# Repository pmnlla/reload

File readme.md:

temp repo before this is moved to hackclub/reflow

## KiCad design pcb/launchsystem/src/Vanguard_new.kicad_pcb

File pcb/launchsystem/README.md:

Rocket launch system - data logging, multiple safety switches, etc

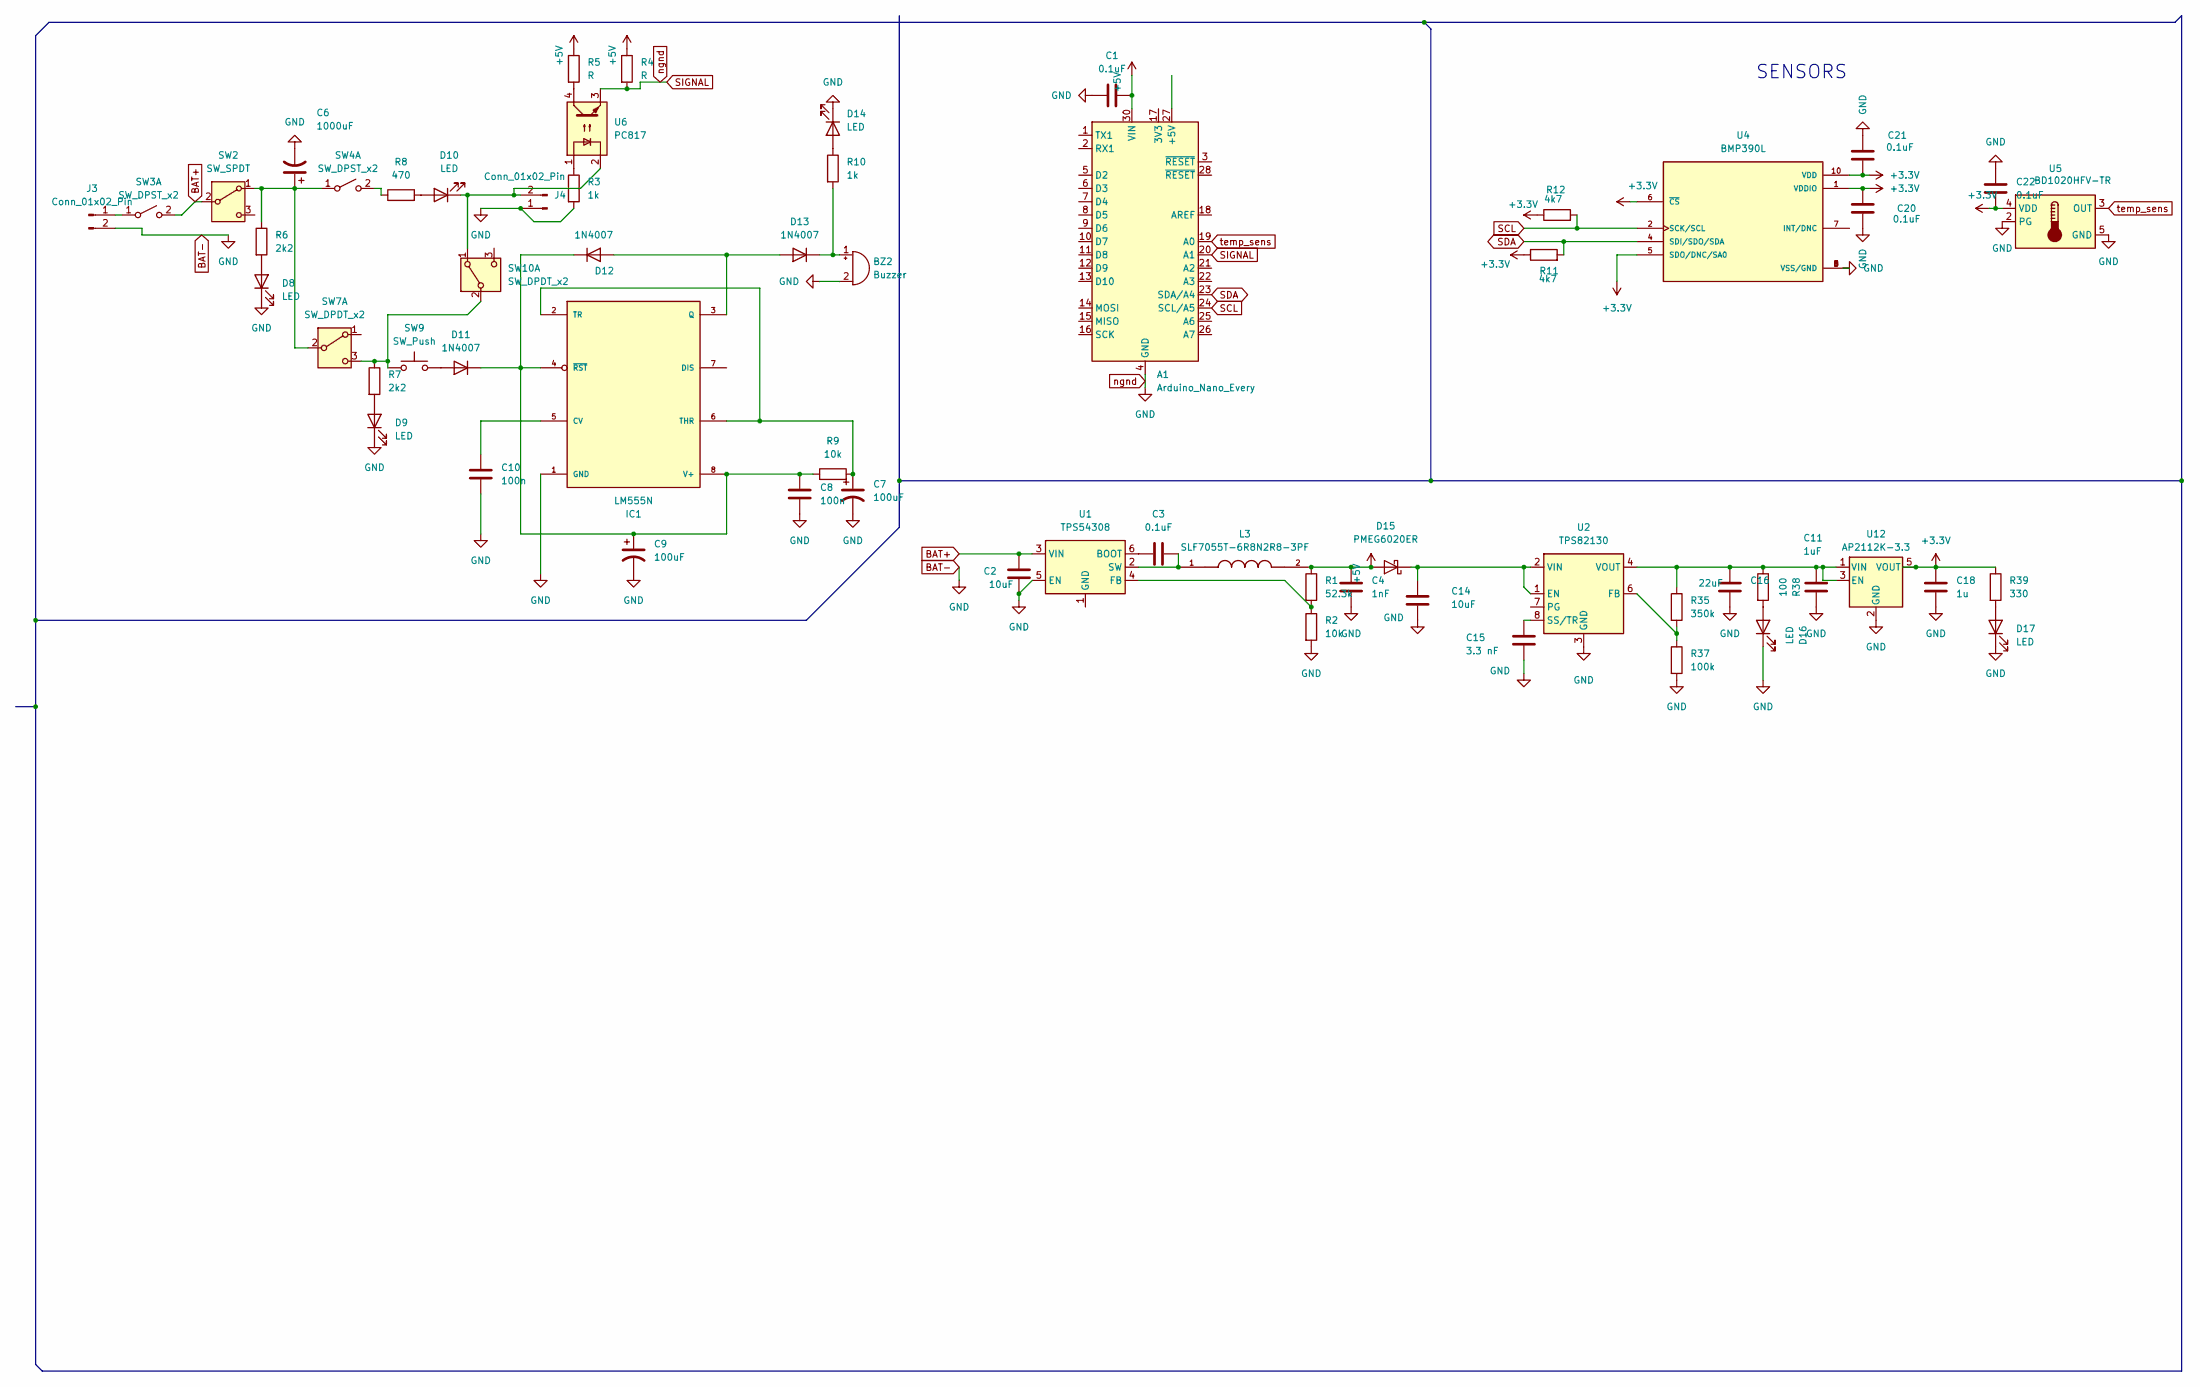
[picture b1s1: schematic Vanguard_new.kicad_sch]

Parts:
A1: Arduino_Nano_Every; Arduino_Nano
BZ2: Buzzer; Buzzer_12x9.5RM7.6
C1, C3, C20, C21, C22: 0.1uF; C_0805_2012Metric
C2, C14: 10uF; C_0805_2012Metric
C4: 1nF; C_0805_2012Metric
C6: 1000uF; C_0805_2012Metric
C7, C9: 100uF; C_0805_2012Metric
C8, C10: 100n; C_0805_2012Metric
C11: 1uF; C_0805_2012Metric
C15: 3.3 nF; C_0805_2012Metric
C16: 22uF; C_0805_2012Metric
C18: 1u; C_0805_2012Metric
D8, D9, D10, D14: LED; LED_D3.0mm
D11, D12, D13: 1N4007; D_SOD-123F
D15: PMEG6020ER; Nexperia_CFP3_SOD-123W
D16, D17: LED; LED_0201_0603Metric
IC1: LM555N; SOIC-8_3.9x4.9mm_P1.27mm
J3: Conn_01x02_Pin; AMASS_XT60-F_1x02_P7.20mm_Vertical
J4: Conn_01x02_Pin; PinSocket_1x02_P2.54mm_Vertical
L3: SLF7055T-6R8N2R8-3PF; L_7.3x7.3_H4.5; PARTREV N/A
R1: 52.3k; R_0805_2012Metric
R2, R9: 10k; R_0805_2012Metric
R3, R10: 1k; R_0805_2012Metric
R4, R5: R; R_0805_2012Metric
R6, R7: 2k2; R_0805_2012Metric
R8: 470; R_0805_2012Metric
R11, R12: 4k7; R_0805_2012Metric
R35: 350k; R_0805_2012Metric
R37: 100k; R_0805_2012Metric
R38: 100; R_0805_2012Metric
R39: 330; R_0805_2012Metric
SW2: SW_SPDT; PinHeader_1x03_P2.54mm_Vertical
SW3, SW4: SW_DPST_x2; PinHeader_1x02_P2.54mm_Vertical
SW7, SW10: SW_DPDT_x2; PinHeader_1x03_P2.54mm_Vertical
SW9: SW_Push; PinHeader_1x02_P2.54mm_Vertical
U1: TPS54308; SOT-23-6
U2: TPS82130; Texas_SIL0008D_MicroSiP-8-1EP_2.8x3mm_P0.65mm_EP1.1x1.9mm_T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
U4: BMP390L; ST_HLGA-10_2x2mm_P0.5mm_LayoutBorder3x2y; PARTREV 1.7
U5: BD1020HFV-TR; HVSOF5
U6: PC817; DIP-4_W7.62mm
U12: AP2112K-3.3; SOT-23-5

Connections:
+3.3V: C18.1, C20.2, C21.1, C22.2, R11.1, R12.1, R39.1, U4.1 (VDDIO), U4.5 (SDO/DNC/SA0), U4.6 (~CS), U4.10 (VDD), U5.4 (VDD), U12.5 (VOUT)
+5V: A1.30 (VIN), C1.2, C4.1, D15.2 (A), L3.2, R1.1, R4.1, R5.1
BAT+: C2.1, SW2.2 (B), SW3.2 (B), U1.3 (VIN)
BAT-: A1.4 (GND), A1.20 (A1), A1.29 (GND), BZ2.2 (-), C1.1, C2.2, C4.2, C6.2, C7.2, C8.2, C9.2, C10.2, C11.2, C14.2, C15.2, C16.2, C18.2, C20.1, C21.2, C22.1, D8.1 (K), D9.1 (K), D14.1 (K), D16.1 (K), D17.1 (K), IC1.1 (GND), J3.2, J4.1, R2.2, R3.2, R4.2, R37.2, U1.5 (EN), U2.3 (GND), U2.9 (GND), U4.3 (VSS/GND), U4.8 (VSS/GND), U4.9 (VSS/GND), U5.2 (PG), U5.5 (GND), U6.3, U12.2 (GND)
unnamed: BZ2.1 (+), D13.1 (K), R10.2
unnamed: D8.2 (A), R6.2
unnamed: D9.2 (A), R7.2
unnamed: D10.2 (A), R8.2
unnamed: D10.1 (K), J4.2, SW10.1 (A), U6.2
unnamed: D11.2 (A), SW9.2
unnamed: C8.1, C9.1, D11.1 (K), D12.1 (K), IC1.4 (~RST), IC1.8 (V+), R9.1
unnamed: D12.2 (A), D13.2 (A), IC1.3 (Q)
unnamed: D14.2 (A), R10.1
unnamed: C14.1, D15.1 (K), U2.1 (EN), U2.2 (VIN)
unnamed: D16.2 (A), R38.2
unnamed: D17.2 (A), R39.2
unnamed: C10.1, IC1.5 (CV)
unnamed: C7.1, IC1.2 (TR), IC1.6 (THR), R9.2
unnamed: J3.1, SW3.1 (A)
unnamed: R3.1, U6.1
unnamed: R5.2, U6.4
unnamed: C6.1, R6.1, SW2.1 (A), SW4.1 (A), SW7.2 (B)
unnamed: R8.1, SW4.2 (B)
unnamed: R7.1, SW7.3 (C), SW9.1, SW10.2 (B)
unnamed: C3.1, U1.6 (BOOT)
unnamed: R1.2, R2.1, U1.4 (FB)
unnamed: C3.2, L3.1, U1.2 (SW)
unnamed: R35.2, R37.1, U2.6 (FB)
unnamed: C15.1, U2.8 (SS/TR)
unnamed: C11.1, C16.1, R35.1, R38.1, U2.4 (VOUT), U2.5 (VOUT), U12.1 (VIN), U12.3 (EN)
SCL: A1.24 (SCL/A5), R12.2, U4.2 (SCK/SCL)
SDA: A1.23 (SDA/A4), R11.2, U4.4 (SDI/SDO/SDA)
temp_sens: A1.19 (A0), U5.3 (OUT)

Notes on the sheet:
SENSORS

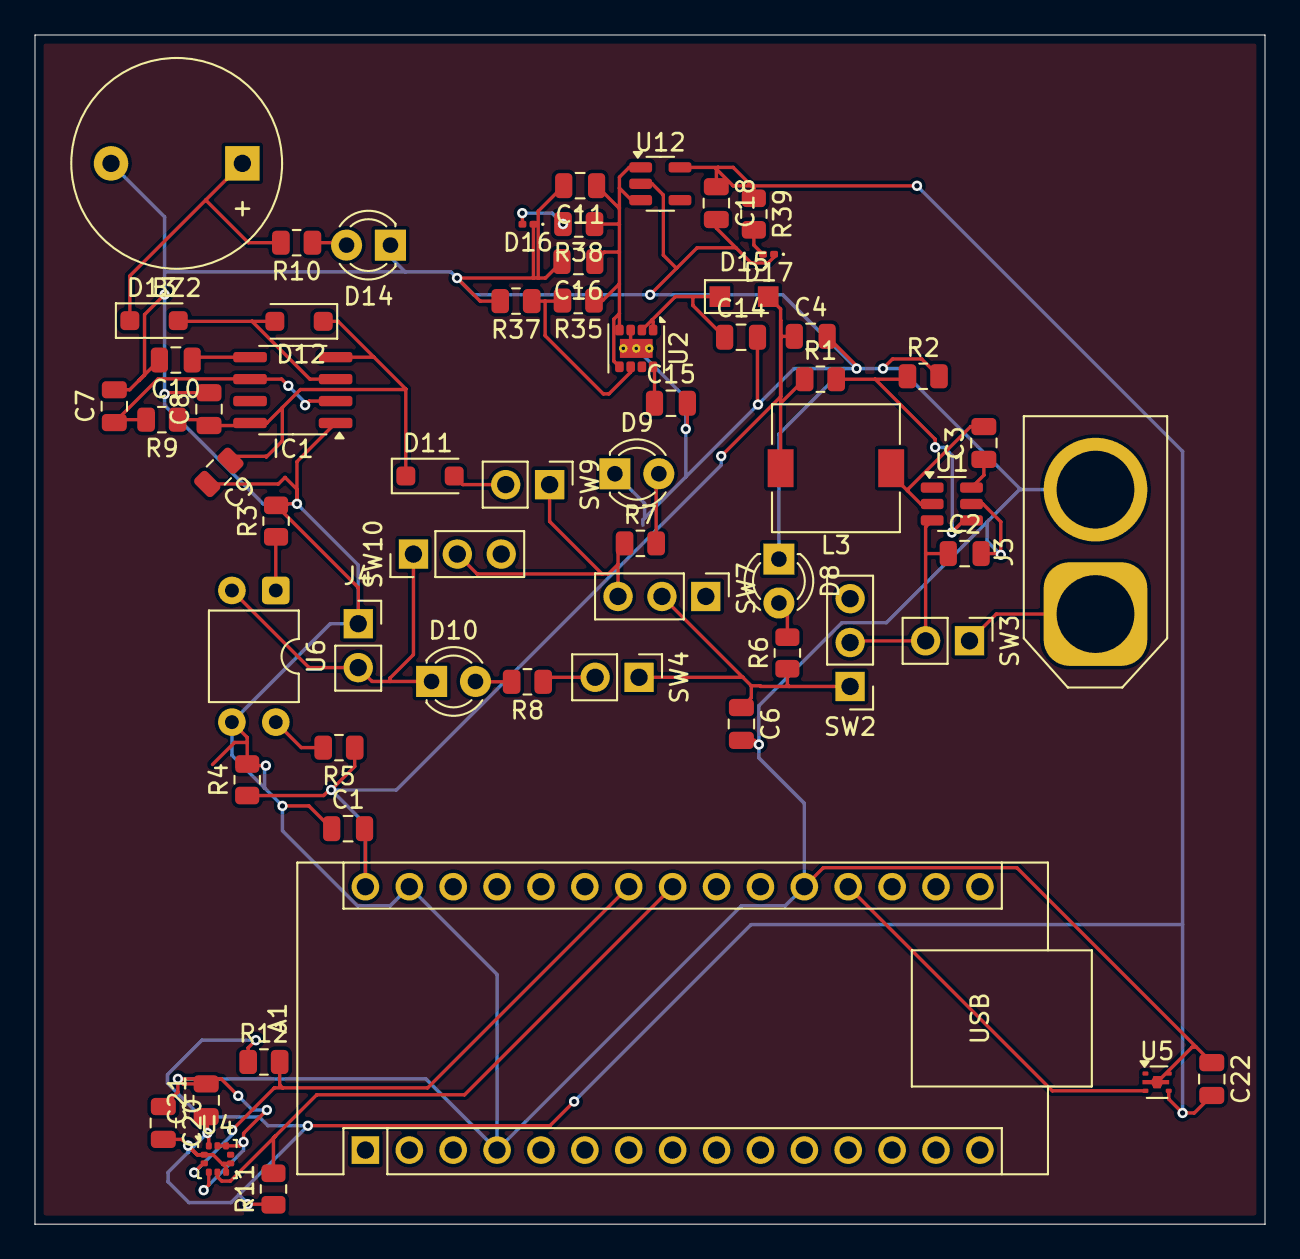
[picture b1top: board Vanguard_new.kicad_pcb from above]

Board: 2 copper layers, 71.2 x 68.8 mm, 61 parts (0 on the bottom side), 33 nets.

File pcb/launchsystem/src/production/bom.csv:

Designator,Footprint,Quantity,Value,LCSC Part #
A1,Arduino_Nano,1,Arduino_Nano_Every,Arduino_Nano_Every
BZ2,Buzzer_12x9.5RM7.6,1,Buzzer,AT-0927-TT-6-R
"C1, C20, C21, C22, C3",805,5,0.1uF,CC0805KRX7R9BB104
"C10, C8",805,2,100n,CC0805KRX7R9BB104
C11,805,1,1uF,CL21B105KBFNNNE
"C14, C2",805,2,10uF,GRM21BR61C106KE15K
C15,805,1,3.3 nF,CC0805KPX7R9BB332
C16,805,1,22uF,CL21A226MQQNNNE
C18,805,1,1u,CL21B105KBFNNNE
C4,805,1,1nF,C0805C102J5GACTU
C6,805,1,1000uF,https://www.amazon.com/McIgIcM-1000uf-capacitor-Aluminum-ele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
"C7, C9",805,2,100uF,GRM21BR60G107ME11L
"D10, D14, D8, D9",LED_D3.0mm,4,LED,151051RS11000
"D11, D12, D13",D_SOD-123F,3,1N4007,1N4007
D15,Nexperia_CFP3_SOD-123W,1,PMEG6020ER,"PMEG6020ER,115"
"D16, D17",201,2,LED,XL-0201UBC
IC1,SOIC-8_3.9x4.9mm_P1.27mm,1,LM555N,https://www.rocelec.com/part/01t4w00000PPpp2AAD-NE555D?utm_t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
J3,AMASS_XT60-F_1x02_P7.20mm_Vertical,1,Conn_01x02_Pin,https://hobbymatehobby.com/products/10pcs-xt90-male-female-b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
,,,,
L3,L_7.3x7.3_H4.5,1,SLF7055T-6R8N2R8-3PF,SLF7055T-6R8N2R8-3PF
R1,805,1,52.3k,CRCW080552K3FKEA
"R10, R3",805,2,1k,RC0805FR-071KL
"R11, R12",805,2,4k7,CRCW08054K70FKEAC
"R2, R9",805,2,10k,RR1220P-103-D
R35,805,1,350k,ERJ-6GEYJ354V
R37,805,1,100k,RC0805FR-07100KL
R38,805,1,100,RC0805FR-07100RL
R39,805,1,330,RC0805FR-07330RL
R4,805,1,0,ERJ-6GEY0R00V
R5,805,1,10K,RR1220P-103-D
"R6, R7",805,2,2k2,CRG0805F2K2
R8,805,1,470,CRGCQ0805J470R
"SW10, SW7",PinHeader_1x03_P2.54mm_Vertical,2,SW_DPDT_x2,https://www.digikey.com/en/products/detail/e-switch/RA111311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
SW2,PinHeader_1x03_P2.54mm_Vertical,1,SW_SPDT,https://www.digikey.com/en/products/detail/e-switch/RA111311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
"SW3, SW4",PinHeader_1x02_P2.54mm_Vertical,2,SW_DPST_x2,https://www.digikey.com/en/products/detail/e-switch/RA111311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
SW9,PinHeader_1x02_P2.54mm_Vertical,1,SW_Push,https://www.amazon.com/Heschen-Toggle-Switch-Position-Waterp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
U1,SOT-23-6,1,TPS54308,TPS54308DDCR
U12,SOT-23-5,1,AP2112K-3.3,AP2112K-3.3TRG1
U2,Texas_SIL0008D_MicroSiP-8-1EP_2.8x3mm_P0.65mm_EP1.1x1.9mm_ThermalVias,1,TPS82130,TPS82130SILR
U4,ST_HLGA-10_2x2mm_P0.5mm_LayoutBorder3x2y,1,BMP390L,BMP390L
U5,HVSOF5,1,BD1020HFV-TR,BD1020HFV-TR
U6,DIP-4_W7.62mm,1,PC817,PC81710NIP1B

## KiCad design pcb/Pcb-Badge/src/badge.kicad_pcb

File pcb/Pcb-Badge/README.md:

# Pcb-Badge
Has e ink display to show name and stuff ,... a thing that you can wear like a id card 
preview
- TOP 

- assembled

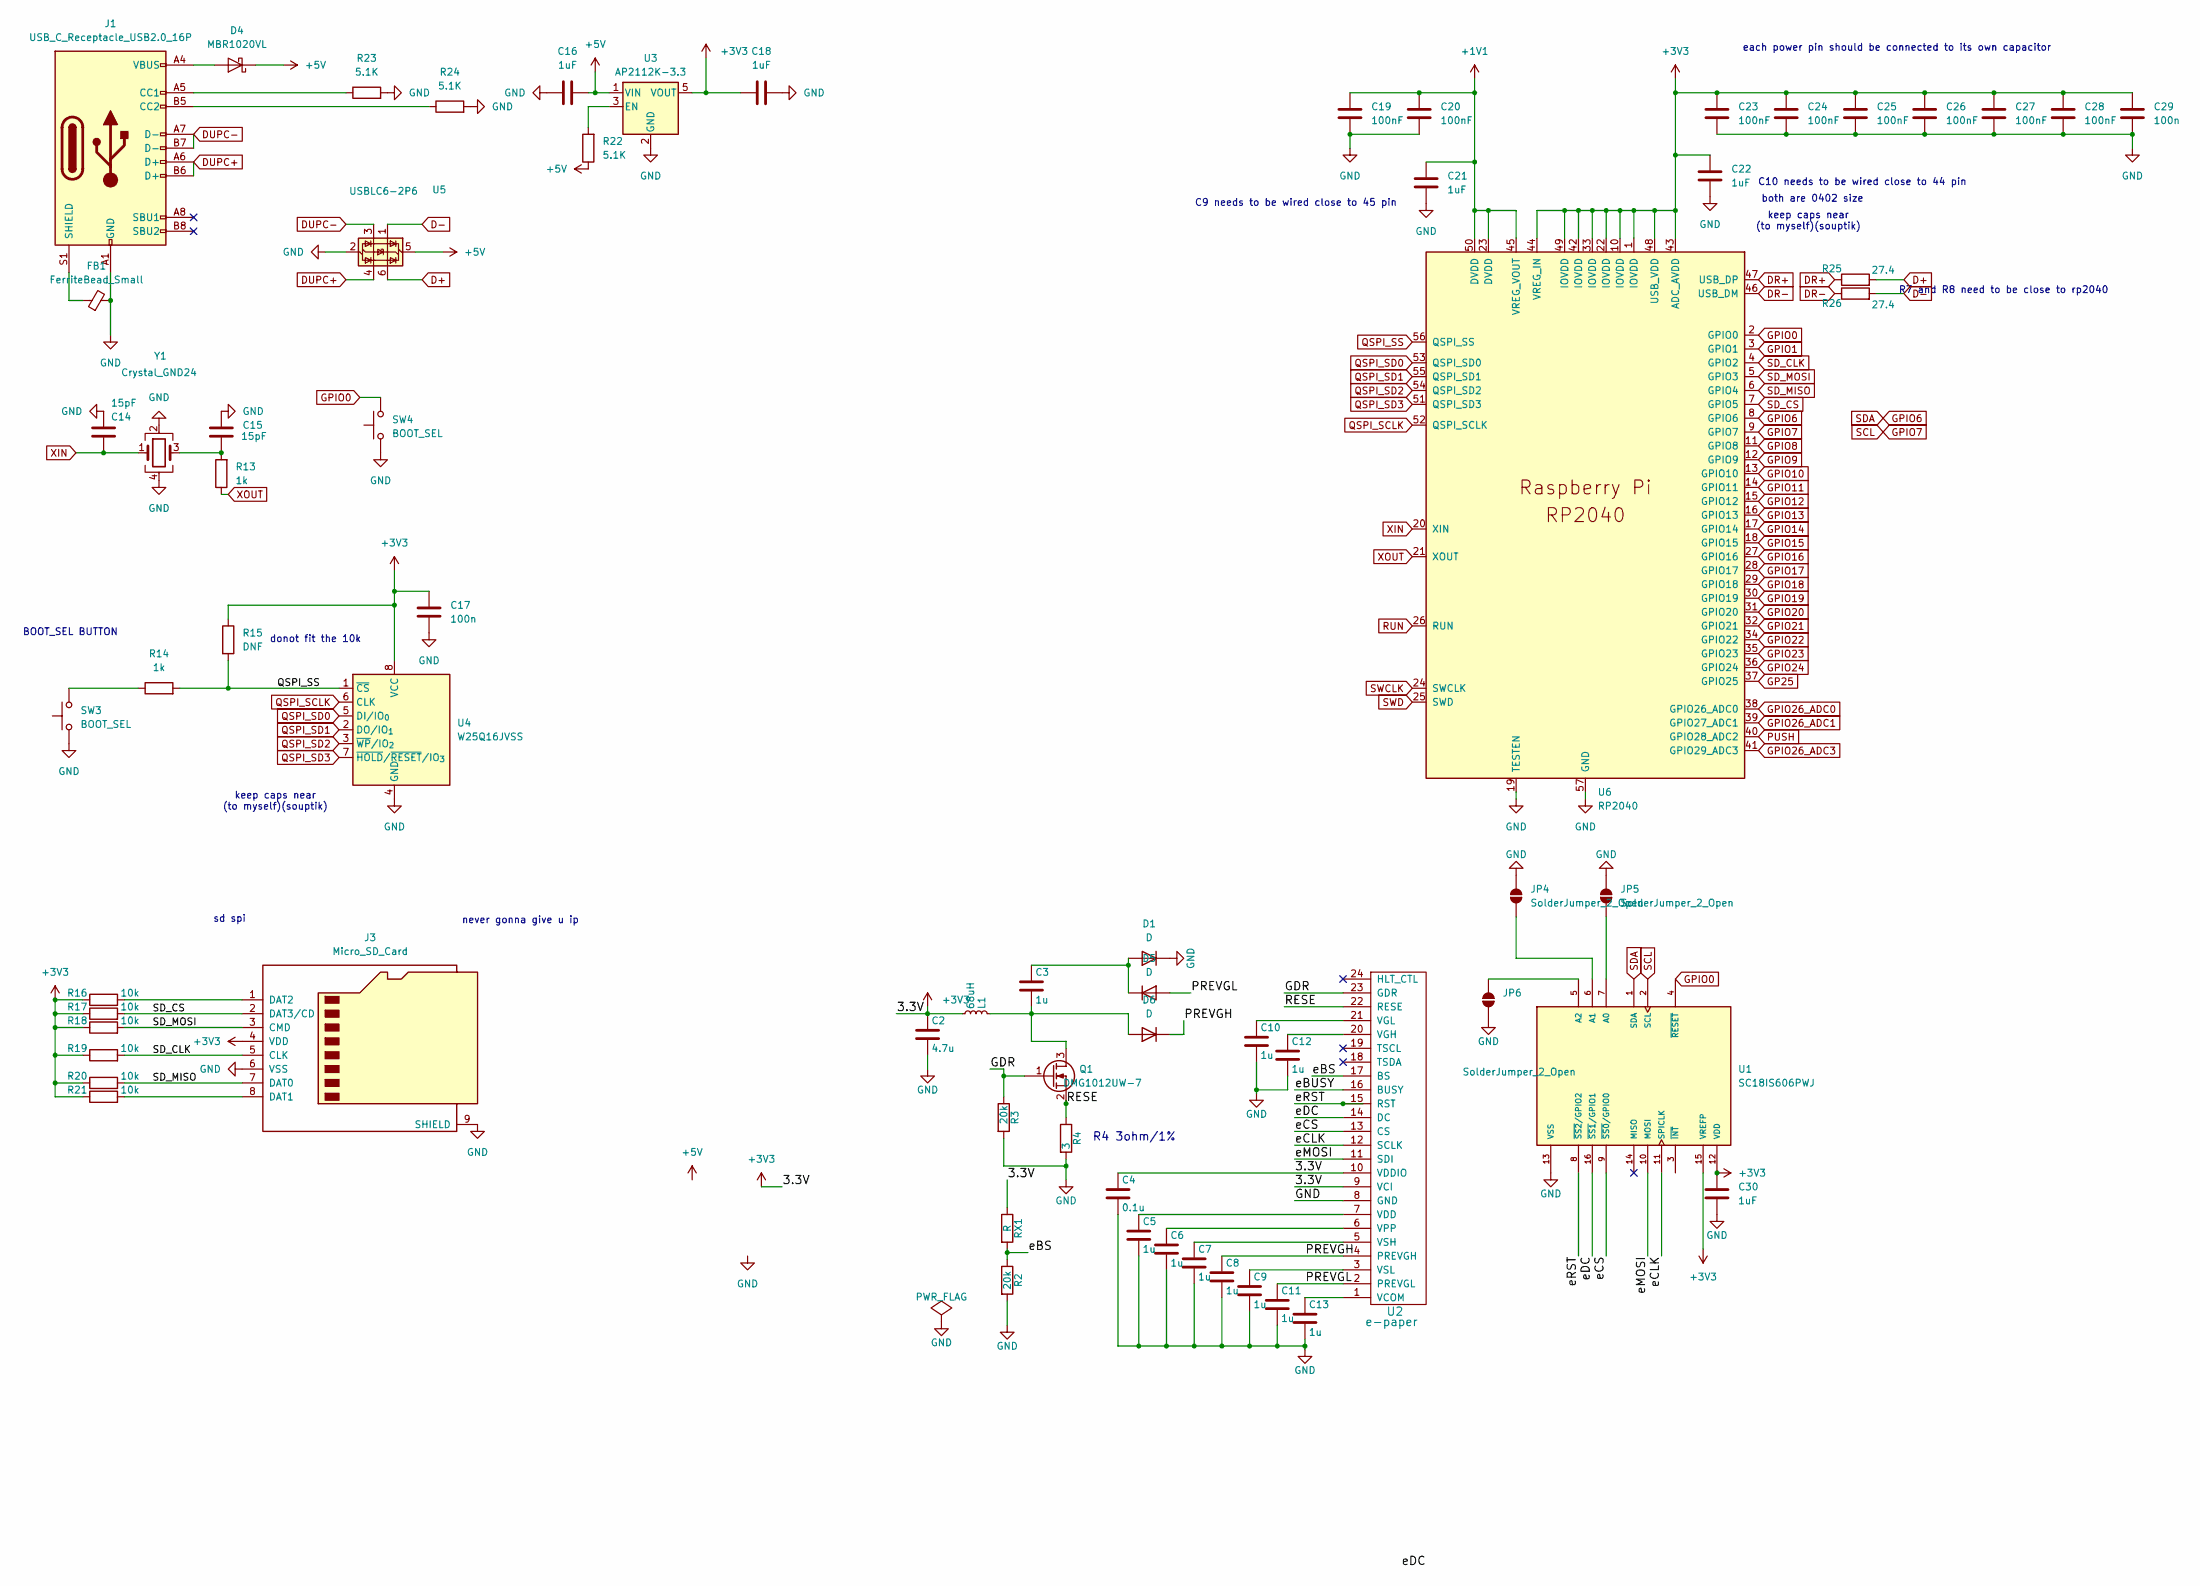
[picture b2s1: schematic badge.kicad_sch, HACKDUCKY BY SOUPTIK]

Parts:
C2: 4.7u; C_0201_0603Metric
C3, C5, C6, C7, C8, C9, C10, C11, C12, C13: 1u; C_0201_0603Metric
C4: 0.1u; C_0201_0603Metric
C14, C15: 15pF; C_0402_1005Metric
C16, C18, C21, C22, C30: 1uF; C_0402_1005Metric
C17, C29: 100n; C_0402_1005Metric
C19, C20, C23, C24, C25, C26, C27, C28: 100nF; C_0402_1005Metric
D1, D5, D6: D; Nexperia_CFP3_SOD-123W
D4: MBR1020VL; D_SOD-123F
FB1: FerriteBead_Small; L_0805_2012Metric_Pad1.15x1.40mm_HandSolder
J1: USB_C_Receptacle_USB2.0_16P; USB_C_Receptacle_GCT_USB4105-xx-A_16P_TopMnt_Horizontal
J3: Micro_SD_Card; microSD_HC_Molex_47219-2001
JP4, JP5, JP6: SolderJumper_2_Open; SolderJumper-2_P1.3mm_Open_RoundedPad1.0x1.5mm
L1: 68uH; L_0805_2012Metric_Pad1.05x1.20mm_HandSolder
Q1: DMG1012UW-7; TSOT-23
R2, R3: 20k; R_0805_2012Metric_Pad1.20x1.40mm_HandSolder
R4: 3; R_0805_2012Metric_Pad1.20x1.40mm_HandSolder
R13, R14: 1k; R_0805_2012Metric_Pad1.20x1.40mm_HandSolder
R15: DNF; R_0805_2012Metric_Pad1.20x1.40mm_HandSolder
R16, R17, R18, R19, R20, R21: 10k; R_0805_2012Metric_Pad1.20x1.40mm_HandSolder
R22, R23, R24: 5.1K; R_0805_2012Metric_Pad1.20x1.40mm_HandSolder
R25, R26: 27.4; R_0805_2012Metric_Pad1.20x1.40mm_HandSolder
RX1: R; R_0805_2012Metric_Pad1.20x1.40mm_HandSolder
SW3, SW4: BOOT_SEL; SW_Push_SPST_NO_Alps_SKRK; LCSC C318884
U1: SC18IS606PWJ; SOP65P640X110-16N; PARTREV 1.0
U2: e-paper; 24pin0.5mm
U3: AP2112K-3.3; SOT-23-5
U4: W25Q16JVSS; SOIC-8_5.3x5.3mm_P1.27mm
U5: USBLC6-2P6; SOT-666
U6: RP2040; QFN-56-1EP_7x7mm_P0.4mm_EP3.2x3.2mm
Y1: Crystal_GND24; Crystal_SMD_Abracon_ABM8G-4Pin_3.2x2.5mm

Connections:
+1V1: C19.1, C20.1, C21.1, U6.23 (DVDD), U6.45 (VREG_VOUT), U6.50 (DVDD)
+3V3: C2.1, C4.1, C17.1, C18.2, C22.1, C23.1, C24.1, C25.1, C26.1, C27.1, C28.1, C29.1, C30.1, J3.4 (VDD), L1.2, R15.1, R16.1, R17.1, R18.1, R19.1, R20.1, R21.1, RX1.1, U1.12 (VDD), U1.15 (VREFP), U2.9 (VCI), U2.10 (VDDIO), U3.5 (VOUT), U4.8 (VCC), U6.1 (IOVDD), U6.10 (IOVDD), U6.22 (IOVDD), U6.33 (IOVDD), U6.42 (IOVDD), U6.43 (ADC_AVDD), U6.44 (VREG_IN), U6.48 (USB_VDD), U6.49 (IOVDD)
+5V: C16.1, D4.1 (K), R22.1, U3.1 (VIN), U5.5 (VBUS)
/GDR: Q1.1 (G), R3.1, U2.23 (GDR)
/PREVGH: C8.1, D6.1 (K), U2.4 (PREVGH)
/PREVGL: C11.1, D5.2 (A), U2.2 (PREVGL)
/RESE: Q1.2 (S), R4.1, U2.22 (RESE)
/eBS: R2.1, RX1.2, U2.17 (BS)
/eBUSY: U2.16 (BUSY)
/eCLK: U1.11 (SPICLK), U2.12 (SCLK)
/eCS: U1.9 (~SS0/GPIO0), U2.13 (CS)
/eDC: U1.16 (~SS1/GPIO1), U2.14 (DC)
/eMOSI: U1.10 (MOSI), U2.11 (SDI)
/eRST: U1.8 (~SS2/GPIO2), U2.15 (RST)
D+: R25.2, U5.6 (I/O1)
D-: R26.2, U5.1 (I/O1)
DR+: R25.1, U6.47 (USB_DP)
DR-: R26.1, U6.46 (USB_DM)
DUPC+: J1.A6 (D+), J1.B6 (D+), U5.4 (I/O2)
DUPC-: J1.A7 (D-), J1.B7 (D-), U5.3 (I/O2)
GND: C2.2, C4.2, C5.2, C6.2, C7.2, C8.2, C9.2, C10.2, C11.2, C12.2, C13.2, C14.2, C15.2, C16.2, C17.2, C18.1, C19.2, C20.2, C21.2, C22.2, C23.2, C24.2, C25.2, C26.2, C27.2, C28.2, C29.2, C30.2, D1.1 (K), FB1.2, J1.A1 (GND), J1.A12 (GND), J1.B1 (GND), J1.B12 (GND), J3.6 (VSS), J3.9 (SHIELD), JP4.2 (B), JP5.2 (B), JP6.1 (A), R2.2, R3.2, R4.2, R23.2, R24.2, SW3.1, SW4.1, U1.13 (VSS), U2.8 (GND), U3.2 (GND), U4.4 (GND), U5.2 (GND), U6.19 (TESTEN), U6.57 (GND), Y1.2, Y1.4
GP25: U6.37 (GPIO25)
GPIO0: SW4.2, U1.4 (~RESET), U6.2 (GPIO0)
GPIO1: U6.3 (GPIO1)
GPIO6: U1.1 (SDA), U6.8 (GPIO6)
GPIO7: U1.2 (SCL), U6.9 (GPIO7)
GPIO8: U6.11 (GPIO8)
GPIO9: U6.12 (GPIO9)
GPIO10: U6.13 (GPIO10)
GPIO11: U6.14 (GPIO11)
GPIO12: U6.15 (GPIO12)
GPIO13: U6.16 (GPIO13)
GPIO14: U6.17 (GPIO14)
GPIO15: U6.18 (GPIO15)
GPIO16: U6.27 (GPIO16)
GPIO17: U6.28 (GPIO17)
GPIO18: U6.29 (GPIO18)
GPIO19: U6.30 (GPIO19)
GPIO20: U6.31 (GPIO20)
GPIO21: U6.32 (GPIO21)
GPIO22: U6.34 (GPIO22)
GPIO23: U6.35 (GPIO23)
GPIO24: U6.36 (GPIO24)
GPIO26_ADC0: U6.38 (GPIO26_ADC0)
GPIO26_ADC1: U6.39 (GPIO27_ADC1)
GPIO26_ADC3: U6.41 (GPIO29_ADC3)
unnamed: C15.1, R13.2, Y1.3
unnamed: C3.1, D1.2 (A), D5.1 (K)
unnamed: D4.2 (A), J1.A4 (VBUS), J1.A9 (VBUS), J1.B4 (VBUS), J1.B9 (VBUS)
unnamed: C3.2, D6.2 (A), L1.1, Q1.3 (D)
unnamed: J1.A5 (CC1), R23.1
unnamed: J1.B5 (CC2), R24.1
unnamed: FB1.1, J1.S1 (SHIELD)
unnamed: J3.8 (DAT1), R21.2
unnamed: J3.1 (DAT2), R16.2
unnamed: JP4.1 (A), U1.6 (A1)
unnamed: JP5.1 (A), U1.7 (A0)
unnamed: JP6.2 (B), U1.5 (A2)
unnamed: R14.1, SW3.2
unnamed: C13.1, U2.1 (VCOM)
unnamed: C5.1, U2.7 (VDD)
unnamed: C12.1, U2.20 (VGH)
unnamed: C10.1, U2.21 (VGL)
unnamed: C6.1, U2.6 (VPP)
unnamed: C7.1, U2.5 (VSH)
unnamed: C9.1, U2.3 (VSL)
unnamed: R22.2, U3.3 (EN)
PUSH: U6.40 (GPIO28_ADC2)
QSPI_SCLK: U4.6 (CLK), U6.52 (QSPI_SCLK)
QSPI_SD0: U4.5 (DI/IO_{0}), U6.53 (QSPI_SD0)
QSPI_SD1: U4.2 (DO/IO_{1}), U6.55 (QSPI_SD1)
QSPI_SD2: U4.3 (~WP/IO_{2}), U6.54 (QSPI_SD2)
QSPI_SD3: U4.7 (~HOLD/~RESET/IO_{3}), U6.51 (QSPI_SD3)
QSPI_SS: R14.2, R15.2, U4.1 (~CS), U6.56 (QSPI_SS)
RUN: U6.26 (RUN)
SD_CLK: J3.5 (CLK), R19.2, U6.4 (GPIO2)
SD_CS: J3.2 (DAT3/CD), R17.2, U6.7 (GPIO5)
SD_MISO: J3.7 (DAT0), R20.2, U6.6 (GPIO4)
SD_MOSI: J3.3 (CMD), R18.2, U6.5 (GPIO3)
SWCLK: U6.24 (SWCLK)
SWD: U6.25 (SWD)
XIN: C14.1, U6.20 (XIN), Y1.1
XOUT: R13.1, U6.21 (XOUT)

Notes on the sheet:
sd spi
never gonna give u ip
donot fit the 10k
BOOT_SEL BUTTON
C9 needs to be wired close to 45 pin
each power pin should be connected to its own capacitor
keep caps near (to myself)(souptik)
C10 needs to be wired close to 44 pin
R4 3ohm/1%
both are 0402 size
R7 and R8 need to be close to rp2040

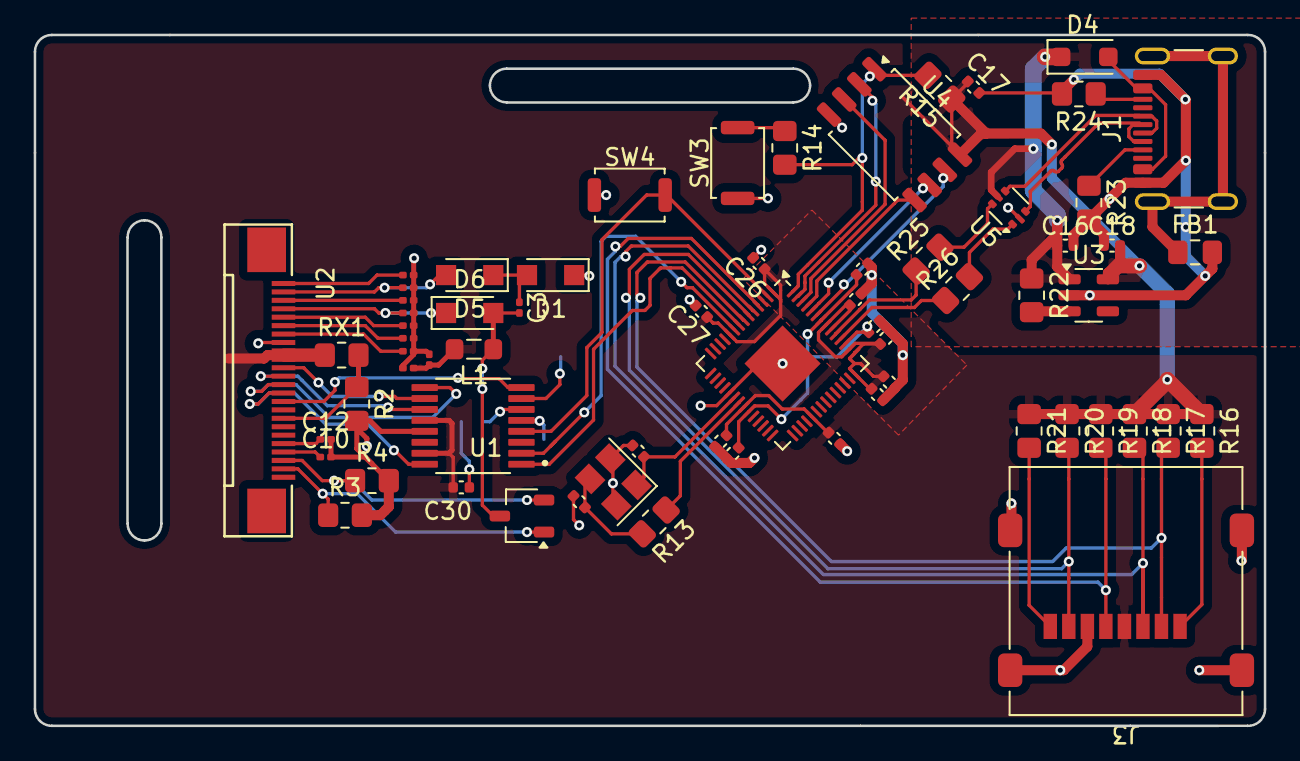
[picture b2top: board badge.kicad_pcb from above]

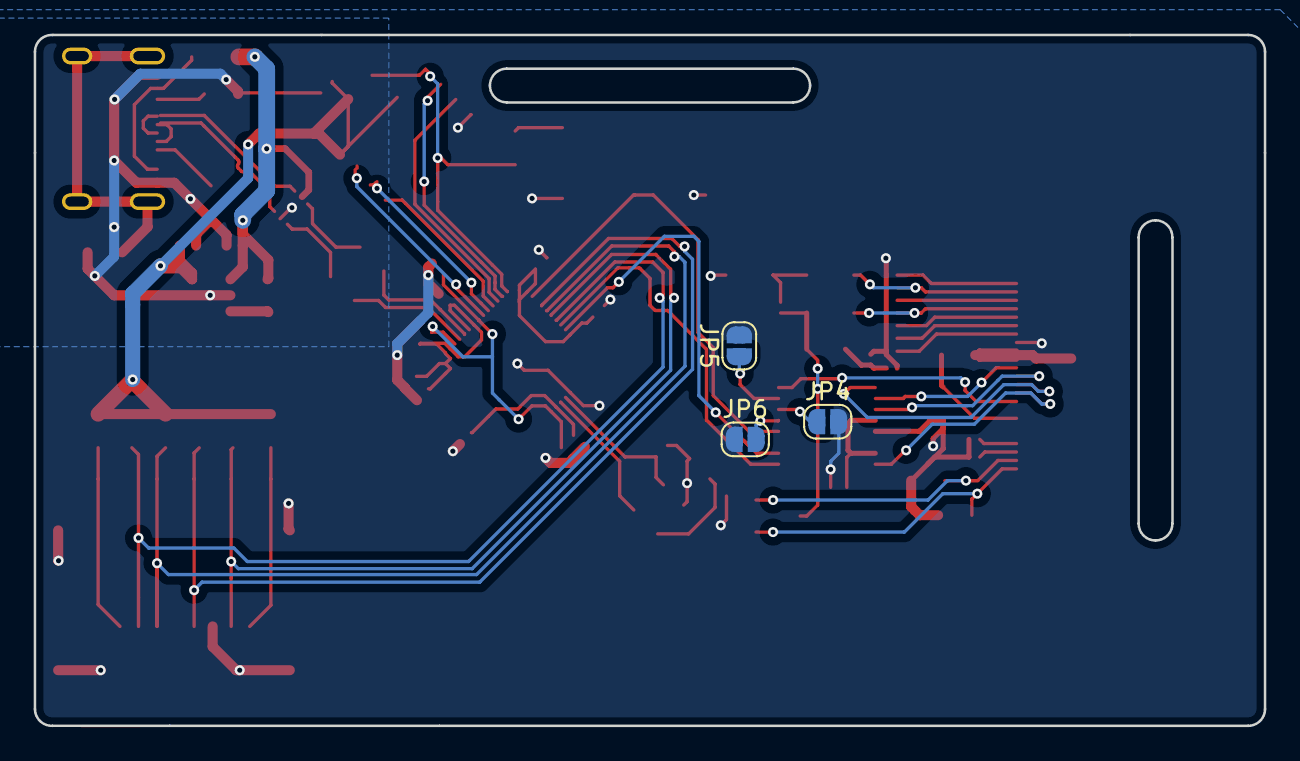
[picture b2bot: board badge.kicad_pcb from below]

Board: 2 copper layers, 73.0 x 41.0 mm, 68 parts (3 on the bottom side), 56 nets.

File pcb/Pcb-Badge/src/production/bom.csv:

Designator,Footprint,Quantity,Value,LCSC Part #
"C10, C11, C12, C13, C3, C5, C6, C7, C8, C9",0201,10,1u,
"C14, C15",0402,2,15pF,
"C16, C18, C21, C22, C30",0402,5,1uF,
"C17, C29",0402,2,100n,
"C19, C20, C23, C24, C25, C26, C27, C28",0402,8,100nF,
C2,0201,1,4.7u,
C4,0201,1,0.1u,
"D1, D5, D6",Nexperia_CFP3_SOD-123W,3,D,
D4,D_SOD-123F,1,MBR1020VL,
FB1,0805,1,FerriteBead_Small,
J1,USB_C_Receptacle_GCT_USB4105-xx-A_16P_TopMnt_Horizontal,1,USB_C_Receptacle_USB2.0_16P,
J3,microSD_HC_Molex_47219-2001,1,Micro_SD_Card,
L1,0805,1,68uH,
Q1,TSOT-23,1,DMG1012UW-7,
"R13, R14",0805,2,1k,
R15,0805,1,DNF,
"R16, R17, R18, R19, R20, R21",0805,6,10k,
"R2, R3",0805,2,20k,
"R22, R23, R24",0805,3,5.1K,
"R25, R26",0805,2,27.4,
R4,0805,1,3,
RX1,0805,1,R,
"SW3, SW4",SW_Push_SPST_NO_Alps_SKRK,2,BOOT_SEL,C318884
U1,SOP65P640X110-16N,1,SC18IS606PWJ,
U2,24pin0.5mm,1,e-paper,
U3,SOT-23-5,1,AP2112K-3.3,
U4,SOIC-8_5.3x5.3mm_P1.27mm,1,W25Q16JVSS,
U5,SOT-666,1,USBLC6-2P6,
U6,QFN-56-1EP_7x7mm_P0.4mm_EP3.2x3.2mm,1,RP2040,
Y1,Crystal_SMD_Abracon_ABM8G-4Pin_3.2x2.5mm,1,Crystal_GND24,

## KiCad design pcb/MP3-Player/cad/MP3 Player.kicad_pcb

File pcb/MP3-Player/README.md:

# MP3 Player

This is a Portable MP3 player which allows one to play music on the even at places where there is no internet access.
You can also view almost all the details you would require while listenting to music on the OLED dispaly that will be connected to it 

Features-
- Atmega328p as a MCU
- DF player MINI (DFR0299) as a MP3 decoder(since i already had it lying around)
- 128x64 0.96 inch OLED display for UI
- Inbuilt charging using TP4056
- 4 iterfacing buttons Play/Pause  Prev/Vol-  Next/Vol+ and RESET for the board 
- Onboard leds for debugging,Power,Charging and Playing status

# PCB

Datasheet [DFR0299](https://wiki.dfrobot.com/DFPlayer_Mini_SKU_DFR0299)

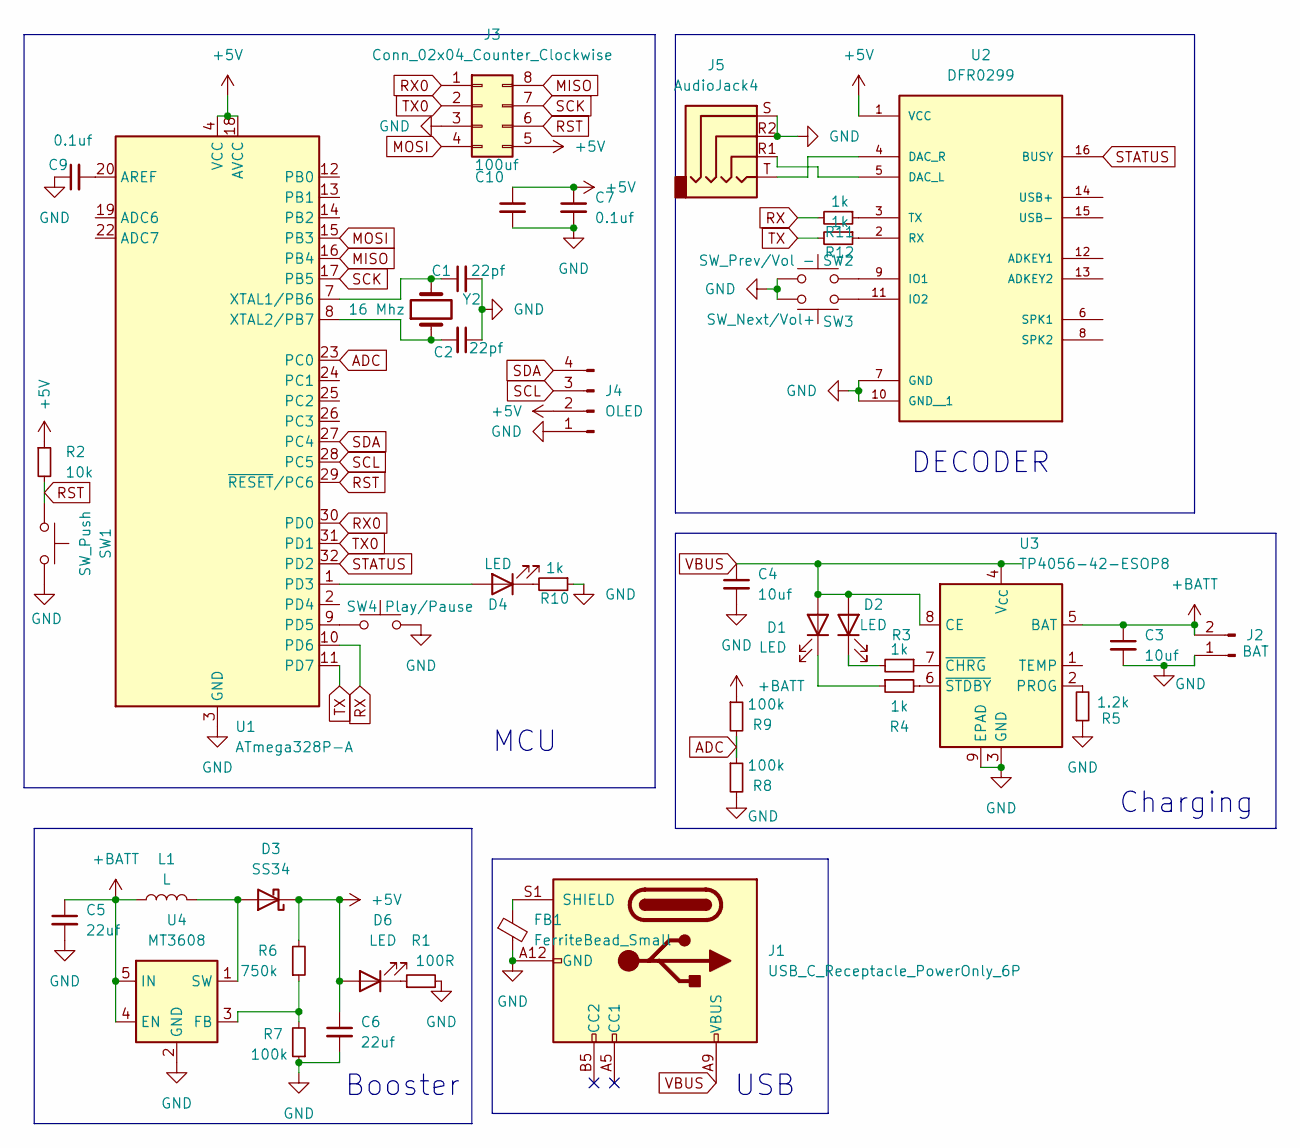
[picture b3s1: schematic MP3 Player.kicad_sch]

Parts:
C1, C2: 22pf; C_0603_1608Metric
C3, C4: 10uf; C_0603_1608Metric
C5, C6: 22uf; C_0603_1608Metric
C7, C9: 0.1uf; C_0603_1608Metric
C10: 100uf; C_1206_3216Metric
D1, D2, D4, D6: LED; LED_0603_1608Metric
D3: SS34; D_SMA
FB1: FerriteBead_Small; R_0805_2012Metric
J1: USB_C_Receptacle_PowerOnly_6P; USB_C_Receptacle_GCT_USB4125-xx-x_6P_TopMnt_Horizontal
J2: BAT; PinHeader_1x02_P2.54mm_Vertical
J3: Conn_02x04_Counter_Clockwise; PinHeader_2x04_P2.54mm_Vertical
J4: OLED; PinHeader_1x04_P2.54mm_Vertical
J5: AudioJack4; Jack_3.5mm_KoreanHropartsElec_PJ-320D-4A_Horizontal
L1: L; L_Bourns_SRP7028A_7.3x6.6mm
R1: 100R; R_0603_1608Metric
R2: 10k; R_0603_1608Metric
R3, R4, R10, R11, R12: 1k; R_0603_1608Metric
R5: 1.2k; R_0603_1608Metric
R6: 750k; R_0603_1608Metric
R7, R8, R9: 100k; R_0603_1608Metric
SW1: SW_Push; SW_SPST_CK_RS282G05A3
SW2: SW_Prev/Vol -; SW_SPST_CK_RS282G05A3
SW3: SW_Next/Vol+; SW_SPST_CK_RS282G05A3
SW4: Play/Pause; SW_SPST_CK_RS282G05A3
U1: ATmega328P-A; TQFP-32_7x7mm_P0.8mm
U2: DFR0299; MODULE_DFR0299
U3: TP4056-42-ESOP8; SOIC-8-1EP_3.9x4.9mm_P1.27mm_EP2.41x3.3mm_ThermalVias
U4: MT3608; SOT-23-6
Y2: 16 Mhz; Crystal_SMD_5032-2Pin_5.0x3.2mm

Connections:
+5V: C6.1, C7.1, C10.1, D3.1 (K), D6.2 (A), J3.5, J4.2, R2.1, R6.2, U1.4 (VCC), U1.6 (VCC), U1.18 (AVCC), U2.1 (VCC); also elsewhere on the board
+BATT: C3.1, C5.1, J2.2, L1.1, R9.1, U3.5 (BAT), U4.4 (EN), U4.5 (IN)
ADC: R8.1, R9.2, U1.23 (PC0)
GND: C1.2, C2.1, C3.2, C4.2, C5.2, C6.2, C7.2, C9.1, C10.2, FB1.2, J1.A12 (GND), J1.B12 (GND), J2.1, J3.3, J4.1, J5.R2, J5.S, R1.2, R5.1, R7.1, R8.2, R10.1, SW1.2, SW2.1, SW3.1, SW4.2, U1.3 (GND), U1.5 (GND), U1.21 (GND), U2.7 (GND), U2.10 (GND__1), U3.3 (GND), U3.9 (EPAD), U4.2 (GND); also elsewhere on the board
MISO: J3.8, U1.16 (PB4)
MOSI: J3.4, U1.15 (PB3)
unnamed: D1.1 (K), R4.1
unnamed: D2.1 (K), R3.2
unnamed: D3.2 (A), L1.2, U4.1 (SW)
unnamed: D4.2 (A), U1.1 (PD3)
unnamed: D4.1 (K), R10.2
unnamed: D6.1 (K), R1.1
unnamed: FB1.1, J1.S1 (SHIELD)
unnamed: C9.2, U1.20 (AREF)
unnamed: SW4.1, U1.9 (PD5)
unnamed: C1.1, U1.7 (XTAL1/PB6), Y2.2
unnamed: C2.2, U1.8 (XTAL2/PB7), Y2.1
unnamed: J5.R1, U2.5 (DAC_L)
unnamed: J5.T, U2.4 (DAC_R)
unnamed: SW2.2, U2.9 (IO1)
unnamed: SW3.2, U2.11 (IO2)
unnamed: R12.1, U2.2 (RX)
unnamed: R11.1, U2.3 (TX)
unnamed: R5.2, U3.2 (PROG)
unnamed: R3.1, U3.7 (~CHRG)
unnamed: R4.2, U3.6 (~STDBY)
unnamed: R6.1, R7.2, U4.3 (FB)
RST: J3.6, R2.2, SW1.1, U1.29 (~RESET/PC6)
RX: R11.2, U1.10 (PD6)
RX0: J3.1, U1.30 (PD0)
SCK: J3.7, U1.17 (PB5)
SCL: J4.3, U1.28 (PC5)
SDA: J4.4, U1.27 (PC4)
STATUS: U1.32 (PD2), U2.16 (BUSY)
TX: R12.2, U1.11 (PD7)
TX0: J3.2, U1.31 (PD1)
VBUS: C4.1, D1.2 (A), D2.2 (A), J1.A9 (VBUS), J1.B9 (VBUS), U3.4 (V_{CC}), U3.8 (CE)

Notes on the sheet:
Booster
Charging
MCU
DECODER
USB

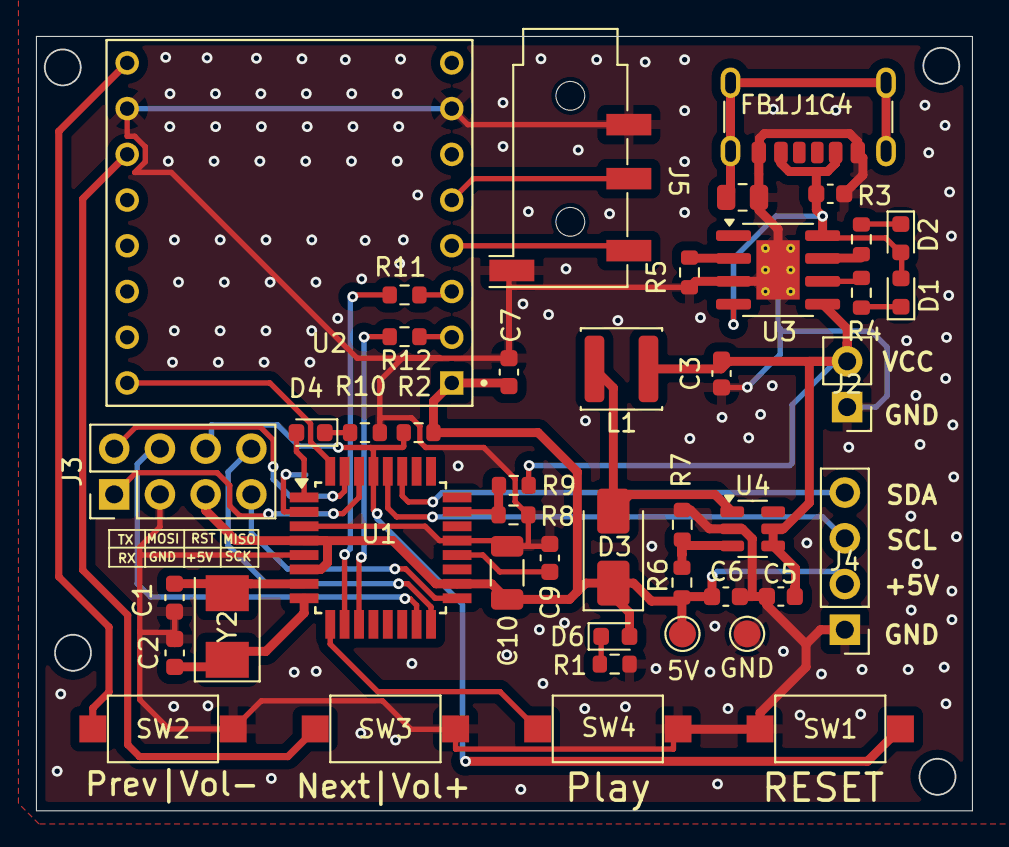
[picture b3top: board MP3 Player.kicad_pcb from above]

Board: 2 copper layers, 52.0 x 43.0 mm, 45 parts (1 on the bottom side), 37 nets.

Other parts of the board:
5V: TestPoint_Pad_D1.5mm
GND: TestPoint_Pad_D1.5mm
GND#2: TestPoint_Pad_D1.0mm

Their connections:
+5V: 5V.1; also elsewhere on the board
GND: GND.1, GND#2.1; also elsewhere on the board
